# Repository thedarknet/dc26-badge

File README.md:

# dc26-badge
Darknet Industries Badge for Defcon 26

Firmware directory has STM32 and ESP32 firmware

hardware has:

* Darknet dc 26 eagle component library library
* Eagle files for board design
* docs for all components on the board plus a number of others that were considered

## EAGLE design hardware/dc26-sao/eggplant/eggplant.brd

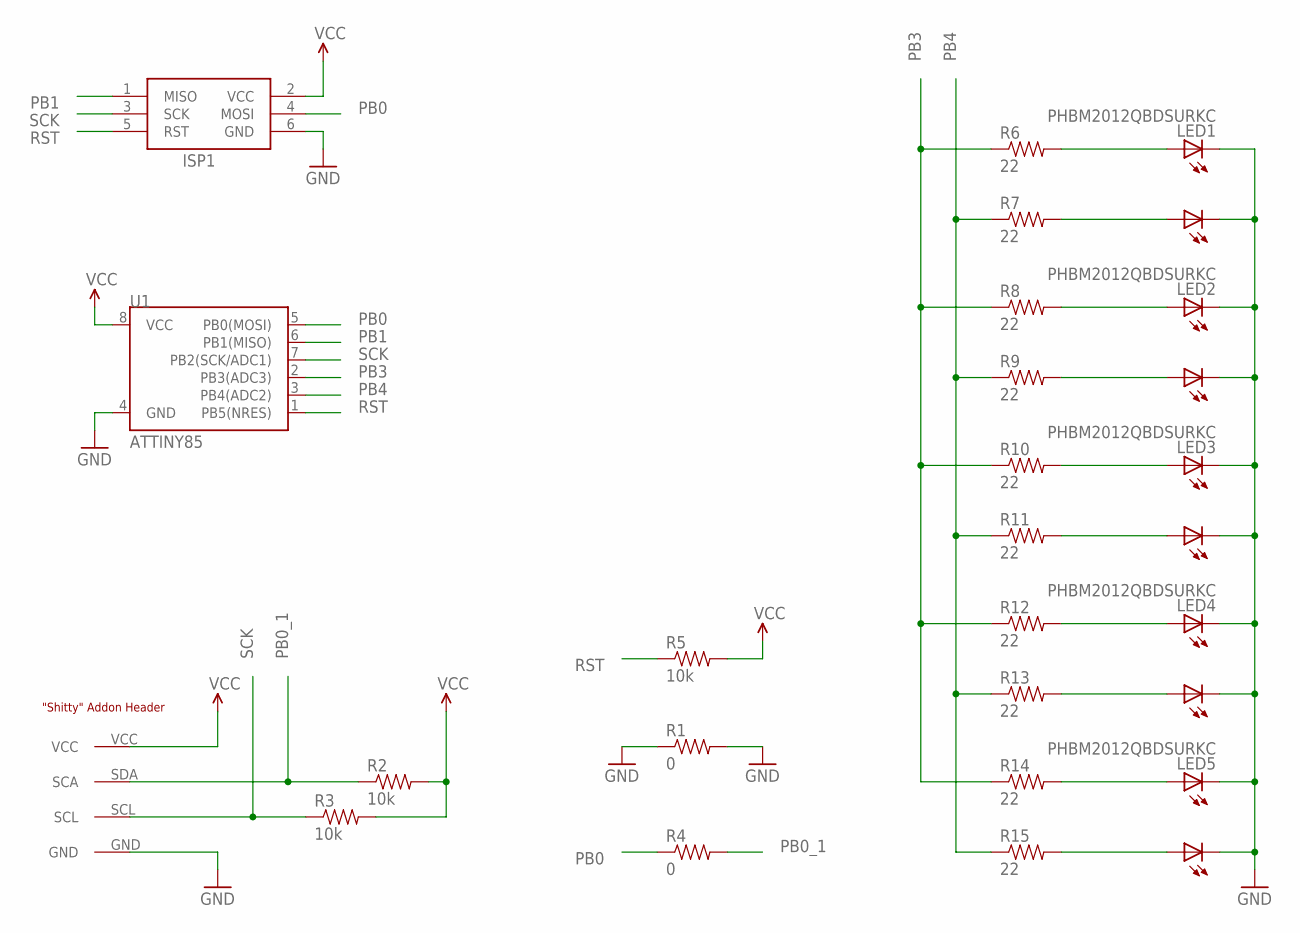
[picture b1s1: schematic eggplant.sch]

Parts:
ISP1: AVRISPPOGO; AVRISP-POGO
LED1, LED2, LED3, LED4, LED5: PHBM2012QBDSURKC; 0805-DUALLED
R1, R4: 0; 0805
R2, R3, R5: 10k; 0603-RES
R6, R7, R8, R9, R10, R11, R12, R13, R14, R15: 22; 0603-RES
U1: ATTINY85; SO08-EIAJ
U$1: ADDONSC_ADDON_SMD; SC_ADDON_SMD

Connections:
GND: ISP1.6 (GND), LED1.CB (C1), LED1.CR (C2), LED2.CB (C1), LED2.CR (C2), LED3.CB (C1), LED3.CR (C2), LED4.CB (C1), LED4.CR (C2), LED5.CB (C1), LED5.CR (C2), R1.1, R1.2, U1.4 (GND), U$1.GND
unnamed: LED1.AB (A1), R6.2
unnamed: LED1.AR (A2), R7.2
unnamed: LED2.AB (A1), R8.2
unnamed: LED2.AR (A2), R9.2
unnamed: LED3.AB (A1), R10.2
unnamed: LED3.AR (A2), R11.2
unnamed: LED4.AB (A1), R12.2
unnamed: LED4.AR (A2), R13.2
unnamed: LED5.AB (A1), R14.2
unnamed: LED5.AR (A2), R15.2
PB0: ISP1.4 (MOSI), R4.1, U1.5 (PB0(MOSI))
PB0_1: R2.1, R4.2, U$1.SDA (SCA)
PB1: ISP1.1 (MISO), U1.6 (PB1(MISO))
PB3: R6.1, R8.1, R10.1, R12.1, R14.1, U1.2 (PB3(ADC3))
PB4: R7.1, R9.1, R11.1, R13.1, R15.1, U1.3 (PB4(ADC2))
RST: ISP1.5 (RST), R5.1, U1.1 (PB5(NRES))
SCK: ISP1.3 (SCK), R3.1, U1.7 (PB2(SCK/ADC1)), U$1.SCL
VCC: ISP1.2 (VCC), R2.2, R3.2, R5.2, U1.8 (VCC), U$1.VCC

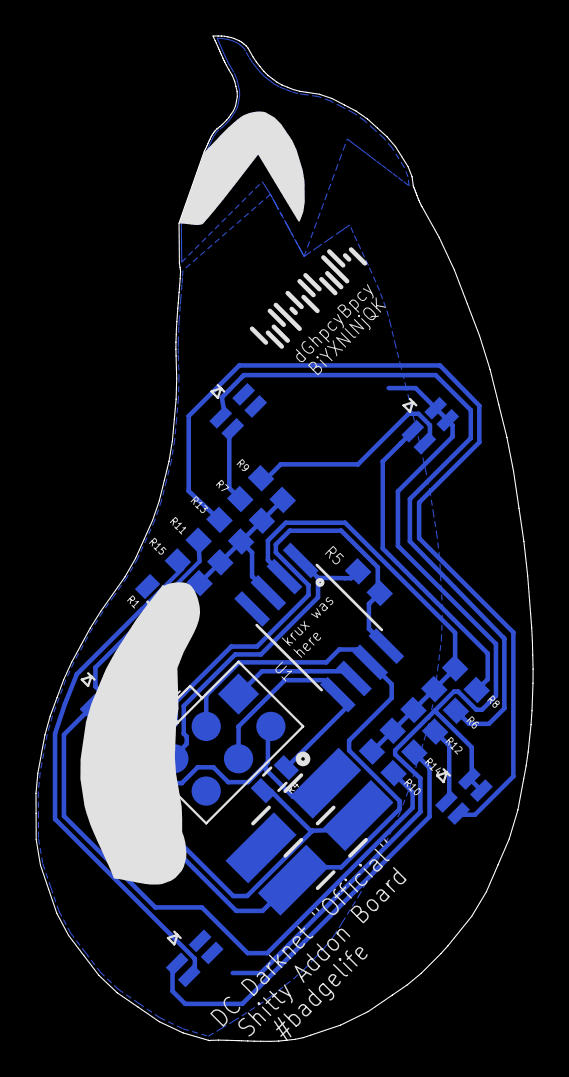
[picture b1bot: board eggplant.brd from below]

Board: 2 copper layers, 27.6 x 55.9 mm, 23 parts (22 on the bottom side), 19 nets.

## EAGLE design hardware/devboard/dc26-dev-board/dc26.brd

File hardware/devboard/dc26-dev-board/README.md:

The darknet board for 2018 (darknet-7) was dc26.brd/sch.
* Things I have not fixed yet:
 * The standard 3mm LEDs are backwards.

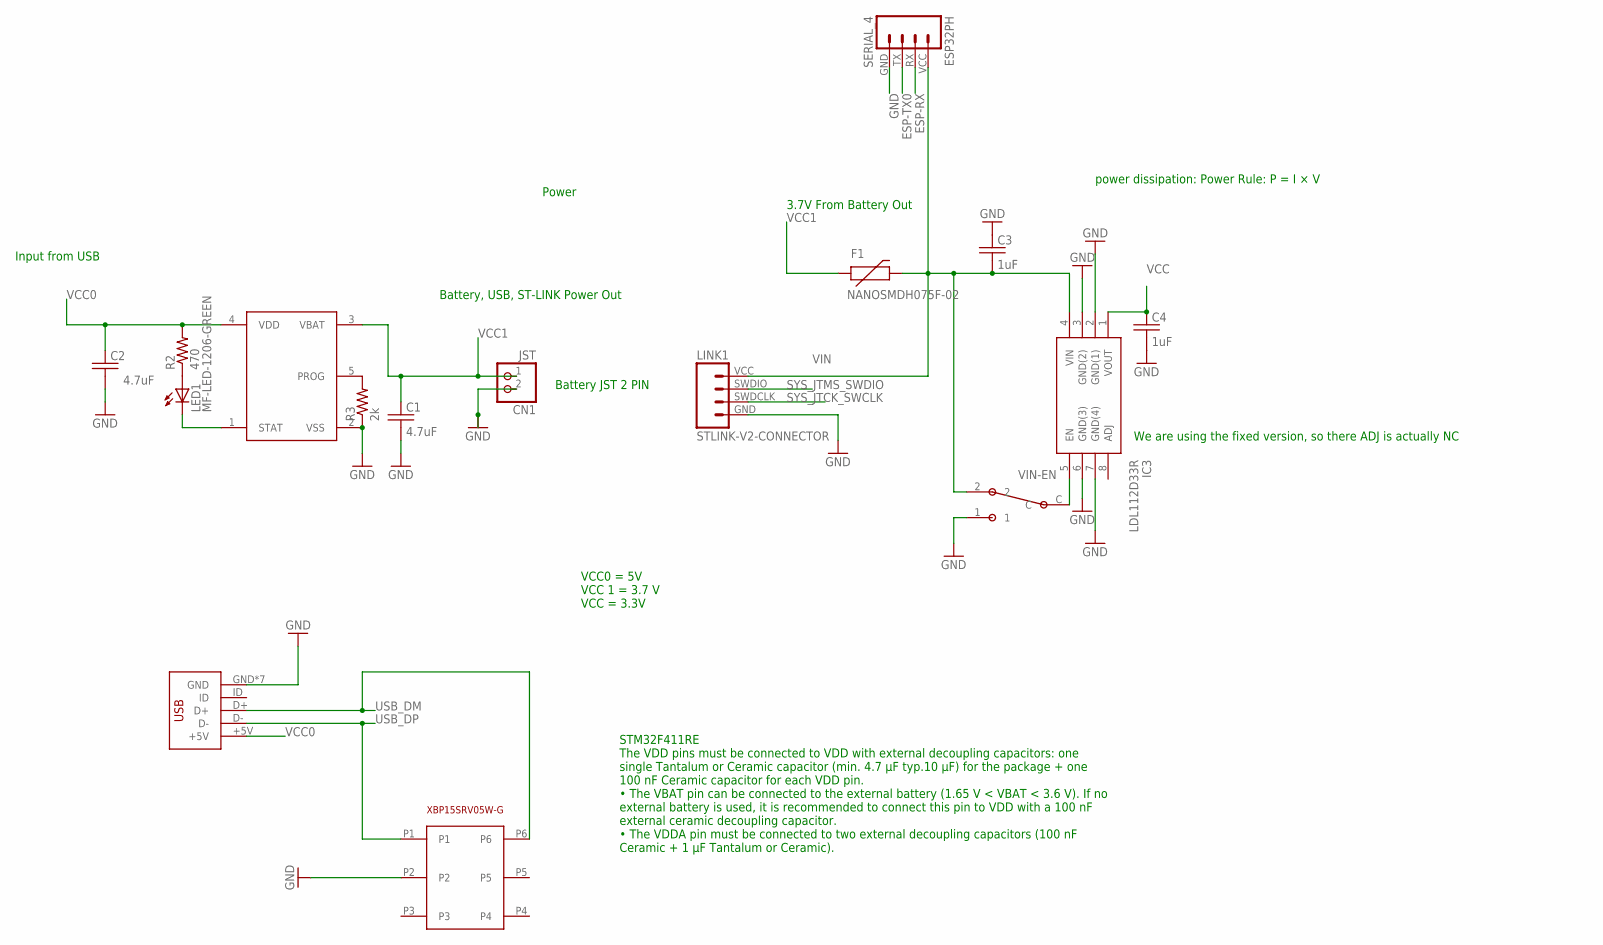
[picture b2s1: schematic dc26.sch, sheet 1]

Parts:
C1, C2: 4.7uF; C0805
C3, C4: 1uF; C0805
CHARGE: MCP73831; SOT23-5
CN1: JST; JST-PH-2-THM-RA
ESP32PH: SERIAL_4; SERIAL_HEADER_4
F1: NANOSMDH075F-02; PTC-1206
IC3: LDL112D33R; SOIC127P600X175-8N
LED1: MF-LED-1206-GREEN; LED-1206
LINK1: STLINK-V2-CONNECTOR; 1X04
P1: SPDT_SSAJ120100
R2: 470; 0805
R3: 2k; 0805
U$17: XBP15SRV05W-G; SOT-26P-XBP15SRV05W-G
USB: DX4R005JJ2DX4R005JJ2; DX4R005JJ2

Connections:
ESP-RX: ESP32PH.RX; also elsewhere on the board
ESP-TX0: ESP32PH.TX; also elsewhere on the board
GND: C1.2, C2.2, C3.1, C4.2, CHARGE.2 (VSS), CN1.2 (1), ESP32PH.GND, IC3.2 (GND(1)), IC3.3 (GND(2)), IC3.6 (GND(3)), IC3.7 (GND(4)), LINK1.GND, P1.1, R3.1, U$17.P2, USB.GND, USB.P$6 (GND), USB.P$7 (GND), USB.P$8 (GND), USB.P$9 (GND), USB.P$10 (GND), USB.P$11 (GND); also elsewhere on the board
unnamed: LED1.A, R2.1
unnamed: CHARGE.5 (PROG), R3.2
unnamed: CHARGE.1 (STAT), LED1.C
SYS_JTCK_SWCLK: LINK1.SWDCLK; also elsewhere on the board
SYS_JTMS_SWDIO: LINK1.SWDIO; also elsewhere on the board
USB_DM: U$17.P6, USB.D+; also elsewhere on the board
USB_DP: U$17.P1, USB.D-; also elsewhere on the board
VCC: C4.1, IC3.1 (VOUT); also elsewhere on the board
VCC0: C2.1, CHARGE.4 (VDD), R2.2, USB.+5V
VCC1: C1.1, CHARGE.3 (VBAT), CN1.1 (2), F1.1; also elsewhere on the board
VIN: C3.2, ESP32PH.VCC, F1.2, IC3.4 (VIN), LINK1.VCC, P1.2; also elsewhere on the board
VIN-EN: IC3.5 (EN), P1.C; also elsewhere on the board

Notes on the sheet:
Input from USB
Battery JST 2 PIN
Battery, USB, ST-LINK Power Out
power dissipation: Power Rule: P = I × V
3.7V From Battery Out
VCC0 = 5V VCC 1 = 3.7 V VCC = 3.3V
Power
STM32F411RE The VDD pins must be connected to VDD with external decoupling capacitors: one single Tantalum or Ceramic capacitor (min. 4.7 μF typ.10 μF) for the package + one 100 nF Ceramic capacitor for each VDD pin. • The VBAT pin can be connected to the external battery (1.65 V < VBAT < 3.6 V). I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
We are using the fixed version, so there ADJ is actually NC

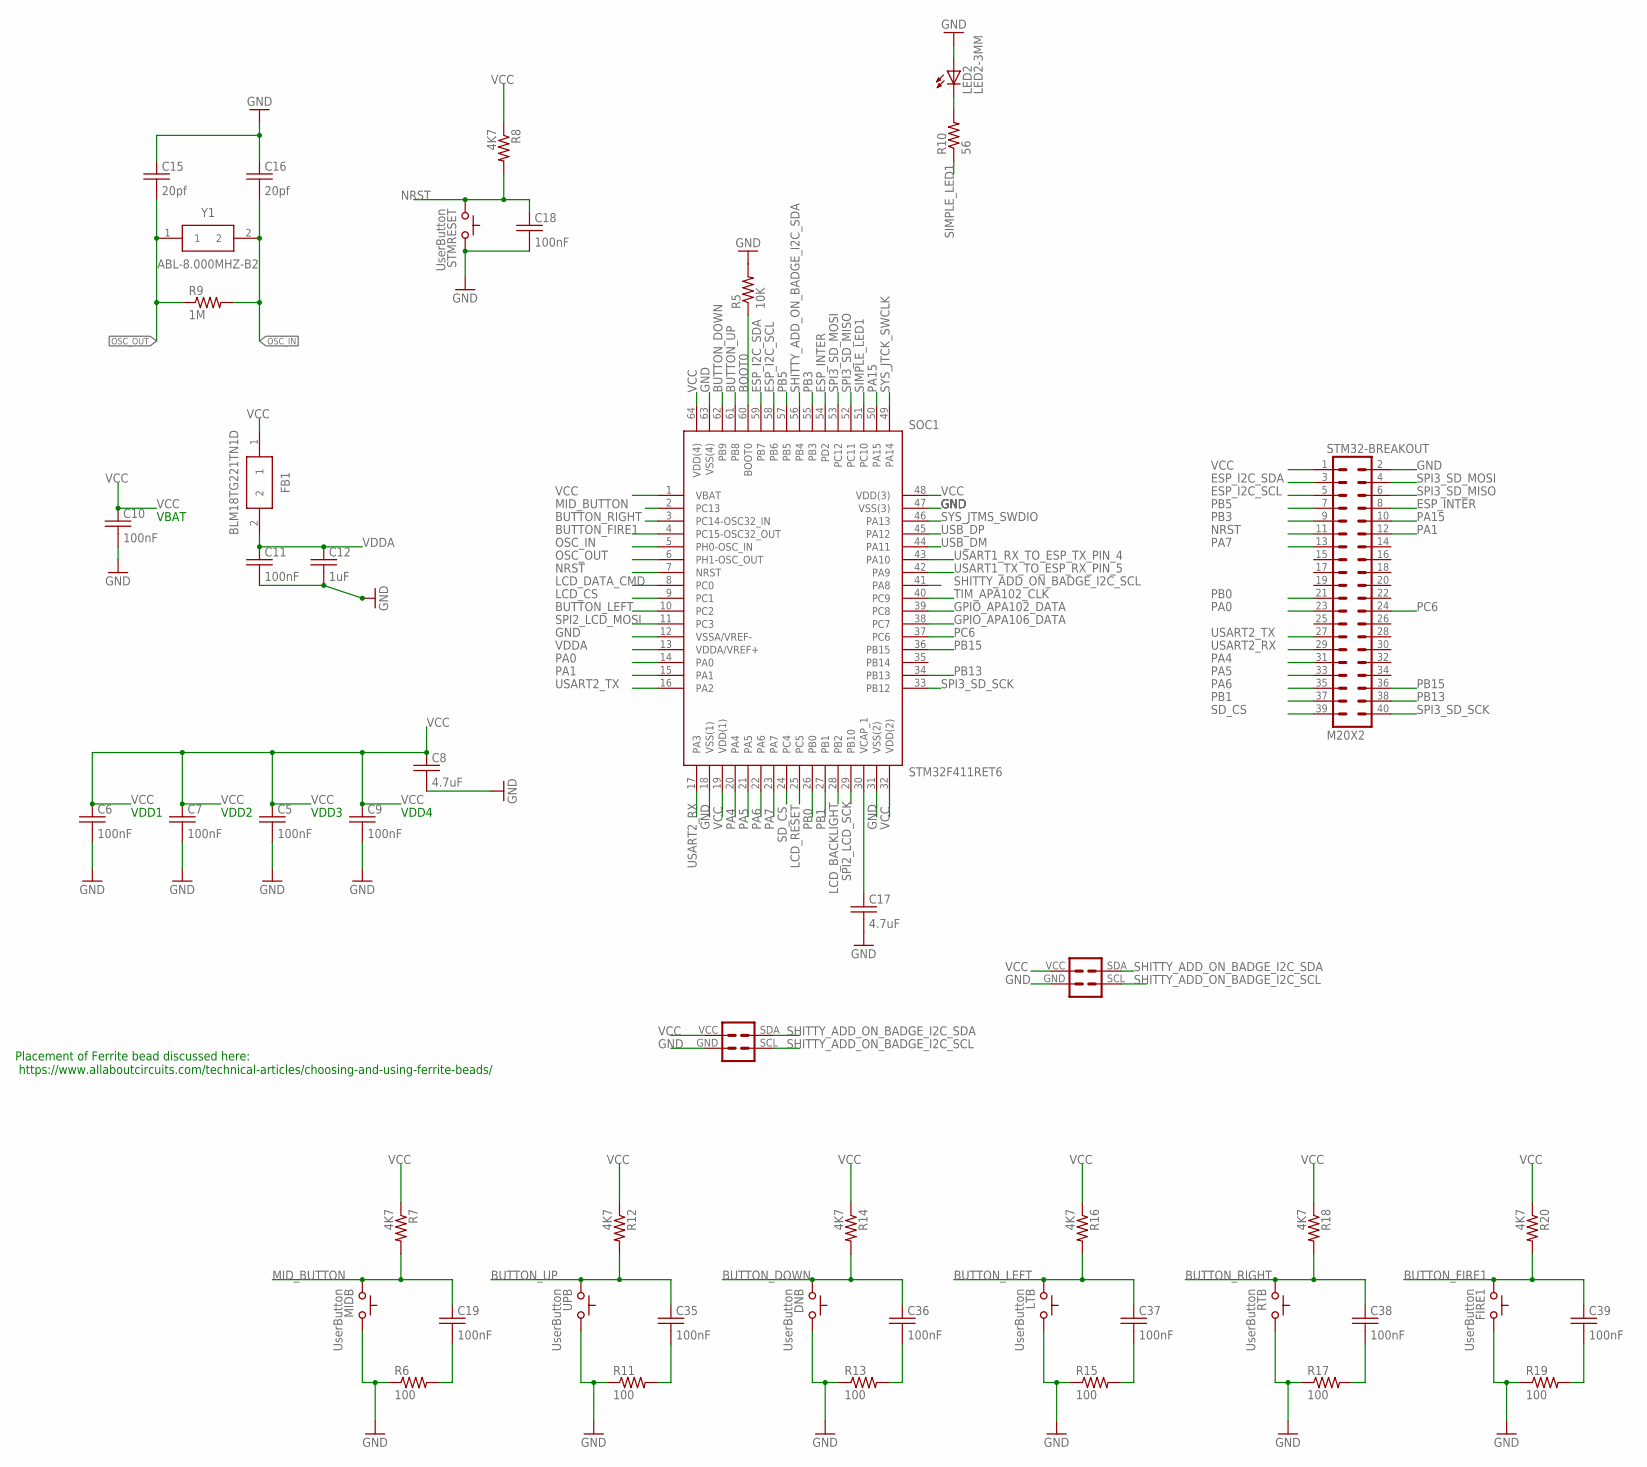
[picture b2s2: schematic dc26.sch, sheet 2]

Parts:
C5, C6, C7, C9, C10, C11, C18, C19, C35, C36, C37, C38, C39: 100nF; C0805
C8, C17: 4.7uF; C0805
C12: 1uF; C0805
C15, C16: 20pf; C0805
DNB: UserButton; TACTILE-2PIN-NARROW
FB1: BLM18TG221TN1D; BEADC1608X75N
FIRE1: UserButton; TACTILE-2PIN-NARROW
J1, J2: DC26 Shitty AddOn; DC26SHITTY_ADDON_CONNECTOR
LED2: LED2-3MM; LED3MM
LTB: UserButton; TACTILE-2PIN-NARROW
MIDB: UserButton; TACTILE-2PIN-NARROW
R5: 10K; 0805
R6, R11, R13, R15, R17, R19: 100; 0805
R7, R8, R12, R14, R16, R18, R20: 4K7; 0805
R9: 1M; 0805
R10: 56; 0805
RTB: UserButton; TACTILE-2PIN-NARROW
SOC1: STM32F411RET6; QFP50P1200X1200X160-64N
STM32-BREAKOUT: M20X2; 2X20
STMRESET: UserButton; TACTILE-2PIN-NARROW
UPB: UserButton; TACTILE-2PIN-NARROW
Y1: ABL-8.000MHZ-B2; HC/49US_(AT49)PTH

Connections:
BOOT0: R5.1, SOC1.60 (BOOT0)
BUTTON_DOWN: C36.1, DNB.P$2 (C), R14.2, SOC1.62 (PB9)
BUTTON_FIRE1: C39.1, FIRE1.P$2 (C), R20.2, SOC1.4 (PC15-OSC32_OUT)
BUTTON_LEFT: C37.1, LTB.P$2 (C), R16.2, SOC1.10 (PC2)
BUTTON_RIGHT: C38.1, R18.2, RTB.P$2 (C), SOC1.3 (PC14-OSC32_IN)
BUTTON_UP: C35.1, R12.2, SOC1.61 (PB8), UPB.P$2 (C)
ESP_I2C_SCL: SOC1.58 (PB6), STM32-BREAKOUT.5; also elsewhere on the board
ESP_I2C_SDA: SOC1.59 (PB7), STM32-BREAKOUT.3; also elsewhere on the board
ESP_INTER: SOC1.54 (PD2), STM32-BREAKOUT.8; also elsewhere on the board
GND: C5.2, C6.2, C7.2, C8.2, C9.2, C10.2, C11.2, C12.2, C15.1, C16.1, C17.2, C18.2, DNB.P$1 (A), FIRE1.P$1 (A), J1.GND, J2.GND, LED2.A, LTB.P$1 (A), MIDB.P$1 (A), R5.2, R6.1, R11.1, R13.1, R15.1, R17.1, R19.1, RTB.P$1 (A), SOC1.12 (VSSA/VREF-), SOC1.18 (VSS(1)), SOC1.31 (VSS(2)), SOC1.47 (VSS(3)), SOC1.63 (VSS(4)), STM32-BREAKOUT.2, STMRESET.P$1 (A), UPB.P$1 (A); also elsewhere on the board
GPIO_APA102_DATA: SOC1.39 (PC8); also elsewhere on the board
GPIO_APA106_DATA: SOC1.38 (PC7); also elsewhere on the board
LCD_BACKLIGHT: SOC1.28 (PB2); also elsewhere on the board
LCD_CS: SOC1.9 (PC1); also elsewhere on the board
LCD_DATA_CMD: SOC1.8 (PC0); also elsewhere on the board
LCD_RESET: SOC1.25 (PC5); also elsewhere on the board
MID_BUTTON: C19.1, MIDB.P$2 (C), R7.2, SOC1.2 (PC13)
unnamed: C19.2, R6.2
unnamed: C17.1, SOC1.30 (VCAP_1)
unnamed: LED2.K (C), R10.2
unnamed: C35.2, R11.2
unnamed: C36.2, R13.2
unnamed: C37.2, R15.2
unnamed: C38.2, R17.2
unnamed: C39.2, R19.2
NRST: C18.1, R8.2, SOC1.7 (NRST), STM32-BREAKOUT.11, STMRESET.P$2 (C)
OSC_IN: C16.2, R9.2, SOC1.5 (PH0-OSC_IN), Y1.2
OSC_OUT: C15.2, R9.1, SOC1.6 (PH1-OSC_OUT), Y1.1
PA0: SOC1.14 (PA0), STM32-BREAKOUT.23
PA1: SOC1.15 (PA1), STM32-BREAKOUT.12
PA4: SOC1.20 (PA4), STM32-BREAKOUT.31
PA5: SOC1.21 (PA5), STM32-BREAKOUT.33
PA6: SOC1.22 (PA6), STM32-BREAKOUT.35
PA7: SOC1.23 (PA7), STM32-BREAKOUT.13
PA15: SOC1.50 (PA15), STM32-BREAKOUT.10
PB0: SOC1.26 (PB0), STM32-BREAKOUT.21
PB1: SOC1.27 (PB1), STM32-BREAKOUT.37
PB3: SOC1.55 (PB3), STM32-BREAKOUT.9
PB5: SOC1.57 (PB5), STM32-BREAKOUT.7
PB13: SOC1.34 (PB13), STM32-BREAKOUT.38
PB15: SOC1.36 (PB15), STM32-BREAKOUT.36
PC6: SOC1.37 (PC6), STM32-BREAKOUT.24
SD_CS: SOC1.24 (PC4), STM32-BREAKOUT.39; also elsewhere on the board
SHITTY_ADD_ON_BADGE_I2C_SCL: J1.SCL, J2.SCL, SOC1.41 (PA8)
SHITTY_ADD_ON_BADGE_I2C_SDA: J1.SDA, J2.SDA, SOC1.56 (PB4)
SIMPLE_LED1: R10.1, SOC1.51 (PC10)
SPI2_LCD_MOSI: SOC1.11 (PC3); also elsewhere on the board
SPI2_LCD_SCK: SOC1.29 (PB10); also elsewhere on the board
SPI3_SD_MISO: SOC1.52 (PC11), STM32-BREAKOUT.6; also elsewhere on the board
SPI3_SD_MOSI: SOC1.53 (PC12), STM32-BREAKOUT.4; also elsewhere on the board
SPI3_SD_SCK: SOC1.33 (PB12), STM32-BREAKOUT.40; also elsewhere on the board
SYS_JTCK_SWCLK: SOC1.49 (PA14); also elsewhere on the board
SYS_JTMS_SWDIO: SOC1.46 (PA13); also elsewhere on the board
TIM_APA102_CLK: SOC1.40 (PC9); also elsewhere on the board
USART1_RX_TO_ESP_TX_PIN_4: SOC1.43 (PA10); also elsewhere on the board
USART1_TX_TO_ESP_RX_PIN_5: SOC1.42 (PA9); also elsewhere on the board
USART2_RX: SOC1.17 (PA3), STM32-BREAKOUT.29
USART2_TX: SOC1.16 (PA2), STM32-BREAKOUT.27
USB_DM: SOC1.44 (PA11); also elsewhere on the board
USB_DP: SOC1.45 (PA12); also elsewhere on the board
VCC: C5.1, C6.1, C7.1, C8.1, C9.1, C10.1, FB1.1, J1.VCC, J2.VCC, R7.1, R8.1, R12.1, R14.1, R16.1, R18.1, R20.1, SOC1.1 (VBAT), SOC1.19 (VDD(1)), SOC1.32 (VDD(2)), SOC1.48 (VDD(3)), SOC1.64 (VDD(4)), STM32-BREAKOUT.1; also elsewhere on the board
VDDA: C11.1, C12.1, FB1.2, SOC1.13 (VDDA/VREF+)

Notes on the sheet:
Placement of Ferrite bead discussed here: https://www.allaboutcircuits.com/technical-articles/choosing-and-using-ferrite-beads/
VBAT
VDD1
VDD2
VDD3
VDD4

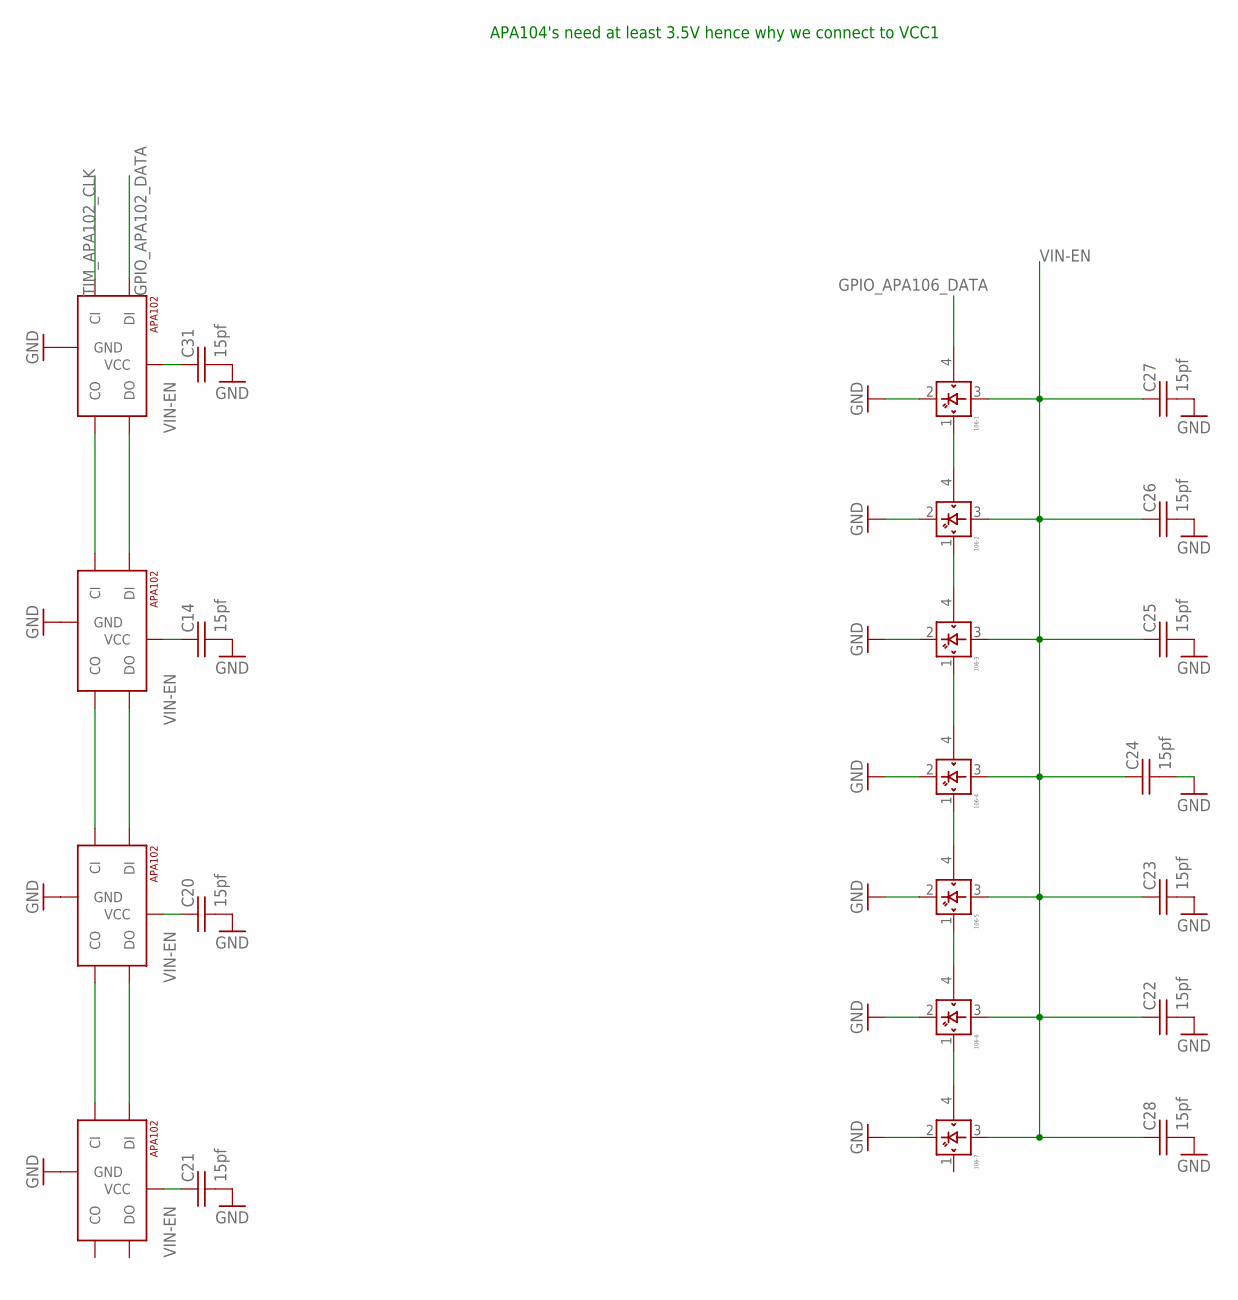
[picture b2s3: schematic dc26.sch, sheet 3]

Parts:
102-1, 102-2, 102-3, 102-4: APA1025050; APA102_5050
106-1, 106-2, 106-3, 106-4, 106-5, 106-6, 106-7: APA-106; WS2812F5_STRAIGHT
C14, C20, C21, C22, C23, C24, C25, C26, C27, C28, C31: 15pf; C0805

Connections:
GND: 102-1.6 (GND), 102-2.6 (GND), 102-3.6 (GND), 102-4.6 (GND), 106-1.2 (GND), 106-2.2 (GND), 106-3.2 (GND), 106-4.2 (GND), 106-5.2 (GND), 106-6.2 (GND), 106-7.2 (GND), C14.2, C20.2, C21.2, C22.2, C23.2, C24.2, C25.2, C26.2, C27.2, C28.2, C31.2; also elsewhere on the board
GPIO_APA102_DATA: 102-1.4 (DI); also elsewhere on the board
GPIO_APA106_DATA: 106-1.4 (DIN); also elsewhere on the board
unnamed: 102-1.2 (CO), 102-2.5 (CI)
unnamed: 102-2.2 (CO), 102-3.5 (CI)
unnamed: 102-3.2 (CO), 102-4.5 (CI)
unnamed: 102-3.3 (DO), 102-4.4 (DI)
unnamed: 102-2.3 (DO), 102-3.4 (DI)
unnamed: 102-1.3 (DO), 102-2.4 (DI)
unnamed: 106-1.1 (DOUT), 106-2.4 (DIN)
unnamed: 106-2.1 (DOUT), 106-3.4 (DIN)
unnamed: 106-3.1 (DOUT), 106-4.4 (DIN)
unnamed: 106-4.1 (DOUT), 106-5.4 (DIN)
unnamed: 106-5.1 (DOUT), 106-6.4 (DIN)
unnamed: 106-6.1 (DOUT), 106-7.4 (DIN)
TIM_APA102_CLK: 102-1.5 (CI); also elsewhere on the board
VIN-EN: 102-1.1 (VCC), 102-2.1 (VCC), 102-3.1 (VCC), 102-4.1 (VCC), 106-1.3 (VDD), 106-2.3 (VDD), 106-3.3 (VDD), 106-4.3 (VDD), 106-5.3 (VDD), 106-6.3 (VDD), 106-7.3 (VDD), C14.1, C20.1, C21.1, C22.1, C23.1, C24.1, C25.1, C26.1, C27.1, C28.1, C31.1; also elsewhere on the board

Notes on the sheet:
APA104's need at least 3.5V hence why we connect to VCC1

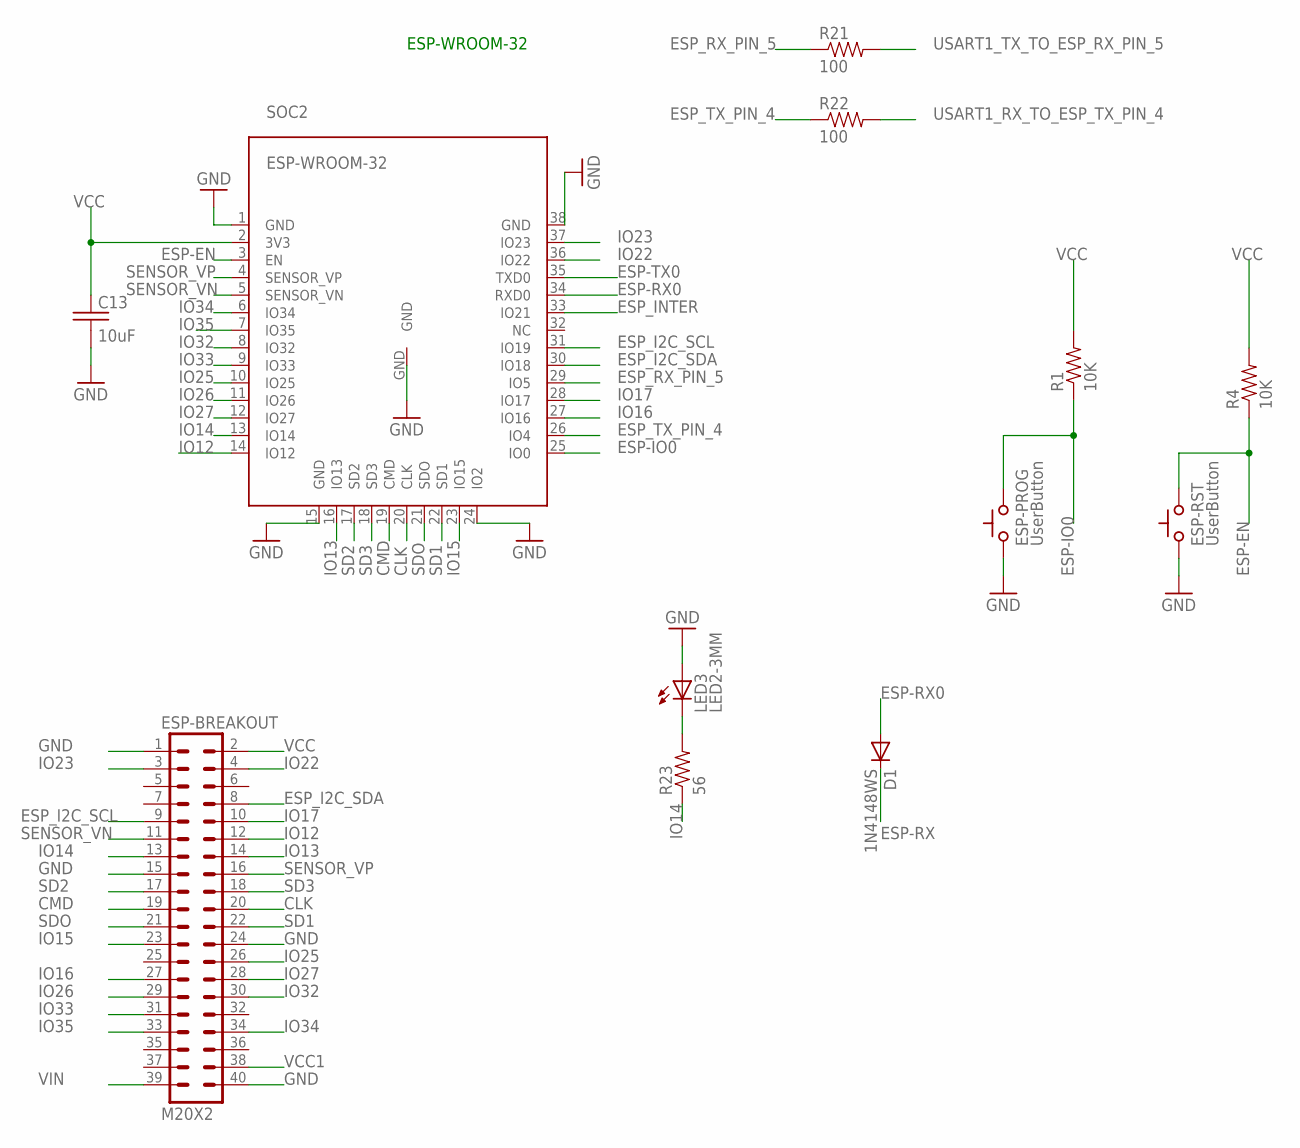
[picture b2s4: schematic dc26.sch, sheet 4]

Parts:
C13: 10uF; C0805
D1: 1N4148WS; SOD-323
ESP-BREAKOUT: M20X2; 2X20
ESP-PROG: UserButton; TACTILE-2PIN-NARROW
ESP-RST: UserButton; TACTILE-2PIN-NARROW
LED3: LED2-3MM; LED3MM
R1, R4: 10K; 0805
R21, R22: 100; 0805
R23: 56; 0805
SOC2: ESP-WROOM-32

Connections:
CLK: ESP-BREAKOUT.20, SOC2.20 (CLK)
CMD: ESP-BREAKOUT.19, SOC2.19 (CMD)
ESP-EN: ESP-RST.P$1 (A), R4.1, SOC2.3 (EN)
ESP-IO0: ESP-PROG.P$1 (A), R1.1, SOC2.25 (IO0)
ESP-RX: D1.1 (C); also elsewhere on the board
ESP-RX0: D1.2 (A), SOC2.34 (RXD0)
ESP-TX0: SOC2.35 (TXD0); also elsewhere on the board
ESP_I2C_SCL: ESP-BREAKOUT.9, SOC2.31 (IO19); also elsewhere on the board
ESP_I2C_SDA: ESP-BREAKOUT.8, SOC2.30 (IO18); also elsewhere on the board
ESP_INTER: SOC2.33 (IO21); also elsewhere on the board
ESP_RX_PIN_5: R21.1, SOC2.29 (IO5)
ESP_TX_PIN_4: R22.1, SOC2.26 (IO4)
GND: C13.2, ESP-BREAKOUT.1, ESP-BREAKOUT.15, ESP-BREAKOUT.24, ESP-BREAKOUT.40, ESP-PROG.P$2 (C), ESP-RST.P$2 (C), LED3.A, SOC2.1 (GND), SOC2.15 (GND), SOC2.24 (IO2), SOC2.38 (GND), SOC2.GND; also elsewhere on the board
IO12: ESP-BREAKOUT.12, SOC2.14 (IO12)
IO13: ESP-BREAKOUT.14, SOC2.16 (IO13)
IO14: ESP-BREAKOUT.13, R23.1, SOC2.13 (IO14)
IO15: ESP-BREAKOUT.23, SOC2.23 (IO15)
IO16: ESP-BREAKOUT.27, SOC2.27 (IO16)
IO17: ESP-BREAKOUT.10, SOC2.28 (IO17)
IO22: ESP-BREAKOUT.4, SOC2.36 (IO22)
IO23: ESP-BREAKOUT.3, SOC2.37 (IO23)
IO25: ESP-BREAKOUT.26, SOC2.10 (IO25)
IO26: ESP-BREAKOUT.29, SOC2.11 (IO26)
IO27: ESP-BREAKOUT.28, SOC2.12 (IO27)
IO32: ESP-BREAKOUT.30, SOC2.8 (IO32)
IO33: ESP-BREAKOUT.31, SOC2.9 (IO33)
IO34: ESP-BREAKOUT.34, SOC2.6 (IO34)
IO35: ESP-BREAKOUT.33, SOC2.7 (IO35)
unnamed: LED3.K (C), R23.2
SD1: ESP-BREAKOUT.22, SOC2.22 (SD1)
SD2: ESP-BREAKOUT.17, SOC2.17 (SD2)
SD3: ESP-BREAKOUT.18, SOC2.18 (SD3)
SDO: ESP-BREAKOUT.21, SOC2.21 (SDO)
SENSOR_VN: ESP-BREAKOUT.11, SOC2.5 (SENSOR_VN)
SENSOR_VP: ESP-BREAKOUT.16, SOC2.4 (SENSOR_VP)
USART1_RX_TO_ESP_TX_PIN_4: R22.2; also elsewhere on the board
USART1_TX_TO_ESP_RX_PIN_5: R21.2; also elsewhere on the board
VCC: C13.1, ESP-BREAKOUT.2, R1.2, R4.2, SOC2.2 (3V3); also elsewhere on the board
VCC1: ESP-BREAKOUT.38; also elsewhere on the board
VIN: ESP-BREAKOUT.39; also elsewhere on the board

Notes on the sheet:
ESP-WROOM-32

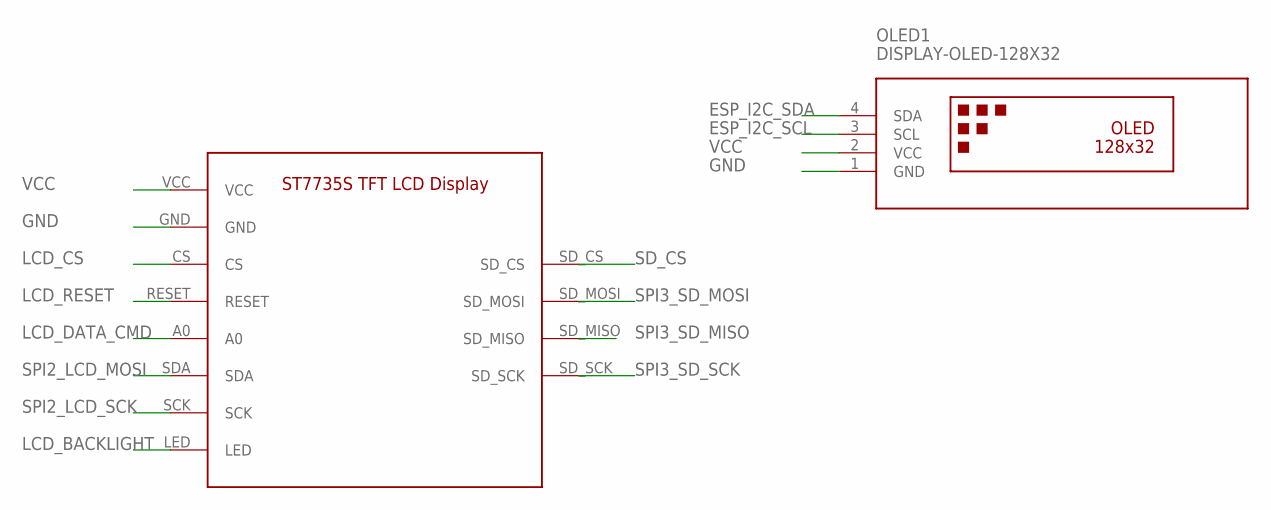
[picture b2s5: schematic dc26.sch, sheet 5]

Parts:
LCD1: ST7735S_LCD_MODULE; ST7735S_LCD_DISPLAY
OLED1: DISPLAY-OLED-128X32

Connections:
ESP_I2C_SCL: OLED1.3 (SCL); also elsewhere on the board
ESP_I2C_SDA: OLED1.4 (SDA); also elsewhere on the board
GND: LCD1.GND, OLED1.1 (GND); also elsewhere on the board
LCD_BACKLIGHT: LCD1.LED; also elsewhere on the board
LCD_CS: LCD1.CS; also elsewhere on the board
LCD_DATA_CMD: LCD1.A0; also elsewhere on the board
LCD_RESET: LCD1.RESET; also elsewhere on the board
SD_CS: LCD1.SD_CS; also elsewhere on the board
SPI2_LCD_MOSI: LCD1.SDA; also elsewhere on the board
SPI2_LCD_SCK: LCD1.SCK; also elsewhere on the board
SPI3_SD_MISO: LCD1.SD_MISO; also elsewhere on the board
SPI3_SD_MOSI: LCD1.SD_MOSI; also elsewhere on the board
SPI3_SD_SCK: LCD1.SD_SCK; also elsewhere on the board
VCC: LCD1.VCC, OLED1.2 (VCC); also elsewhere on the board

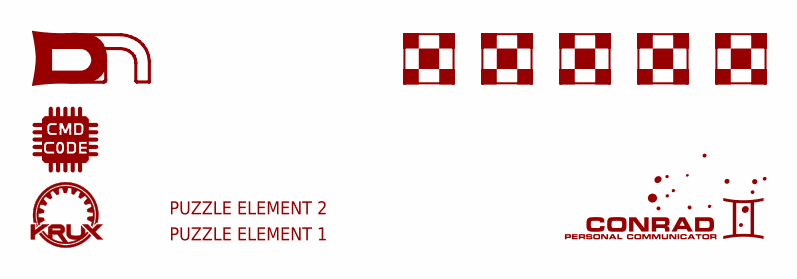
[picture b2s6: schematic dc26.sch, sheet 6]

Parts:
U$1: KRUX_LOGO
U$2: CMD_C0DE_LOGO
U$3: DC26_KRUX_PUZZLE_1; DN26_KRUX_PUZZLE_1
U$4: DC26_KRUX_PUZZLE_2; DN26_KRUX_PUZZLE_2
U$5: CONRAD_LOGO
U$6: DN_LOGODC26; DN_LOGO_DC26
U$7, U$8: FIDUCIAL_DNBOX; FIDUCIAL_BOX
U$9, U$10, U$11: FIDUCIAL_DNCORNER; FIDUCIAL_CORNER

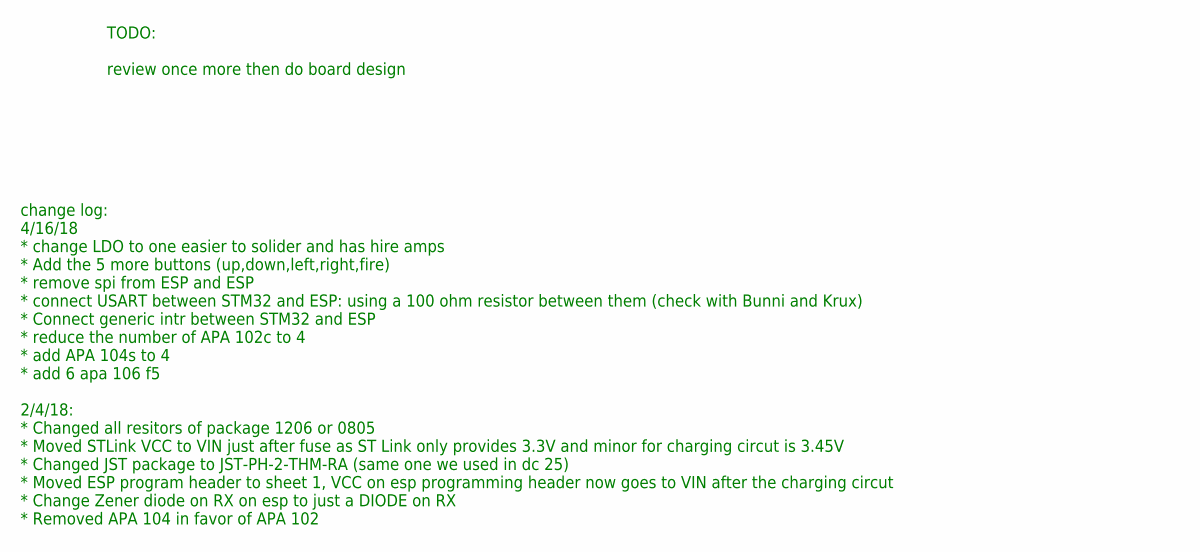
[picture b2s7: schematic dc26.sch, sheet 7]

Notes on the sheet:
change log: 4/16/18 * change LDO to one easier to solider and has hire amps * Add the 5 more buttons (up,down,left,right,fire) * remove spi from ESP and ESP * connect USART between STM32 and ESP: using a 100 ohm resistor between them (check with Bunni and Krux) * Connect generic intr between STM32 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
TODO: review once more then do board design

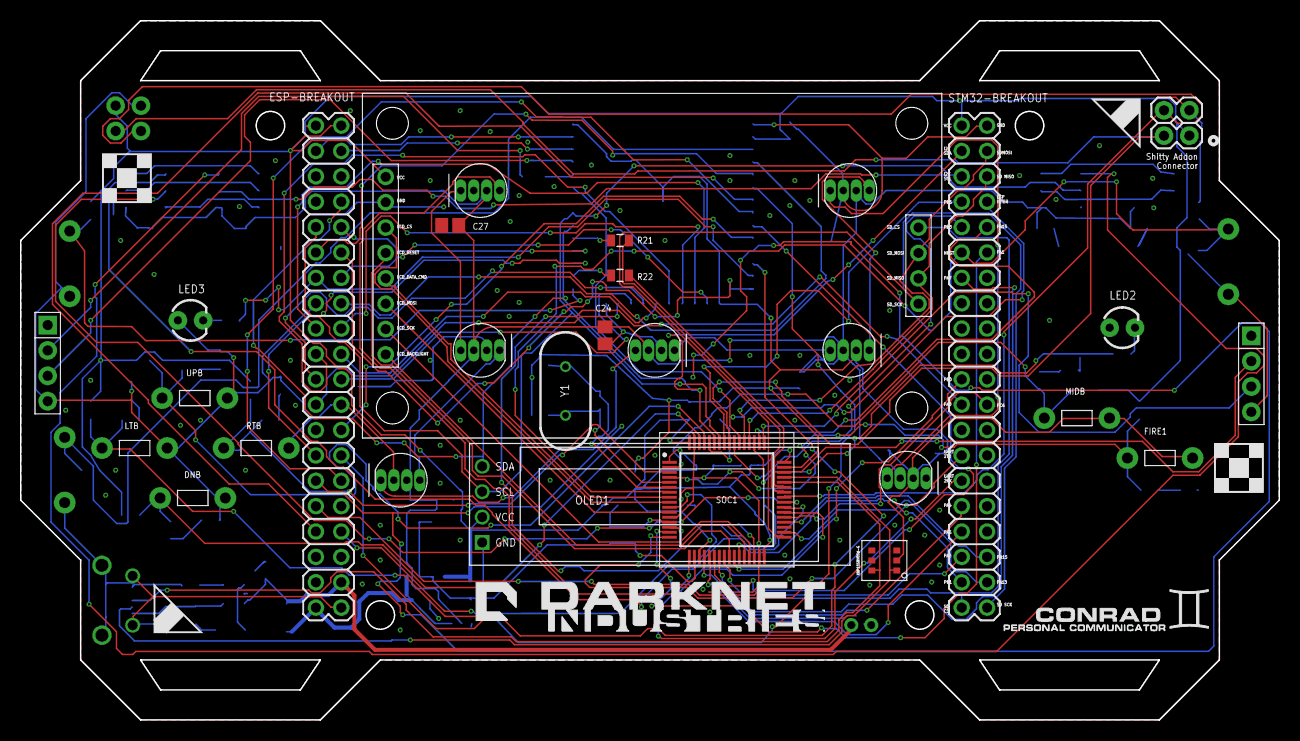
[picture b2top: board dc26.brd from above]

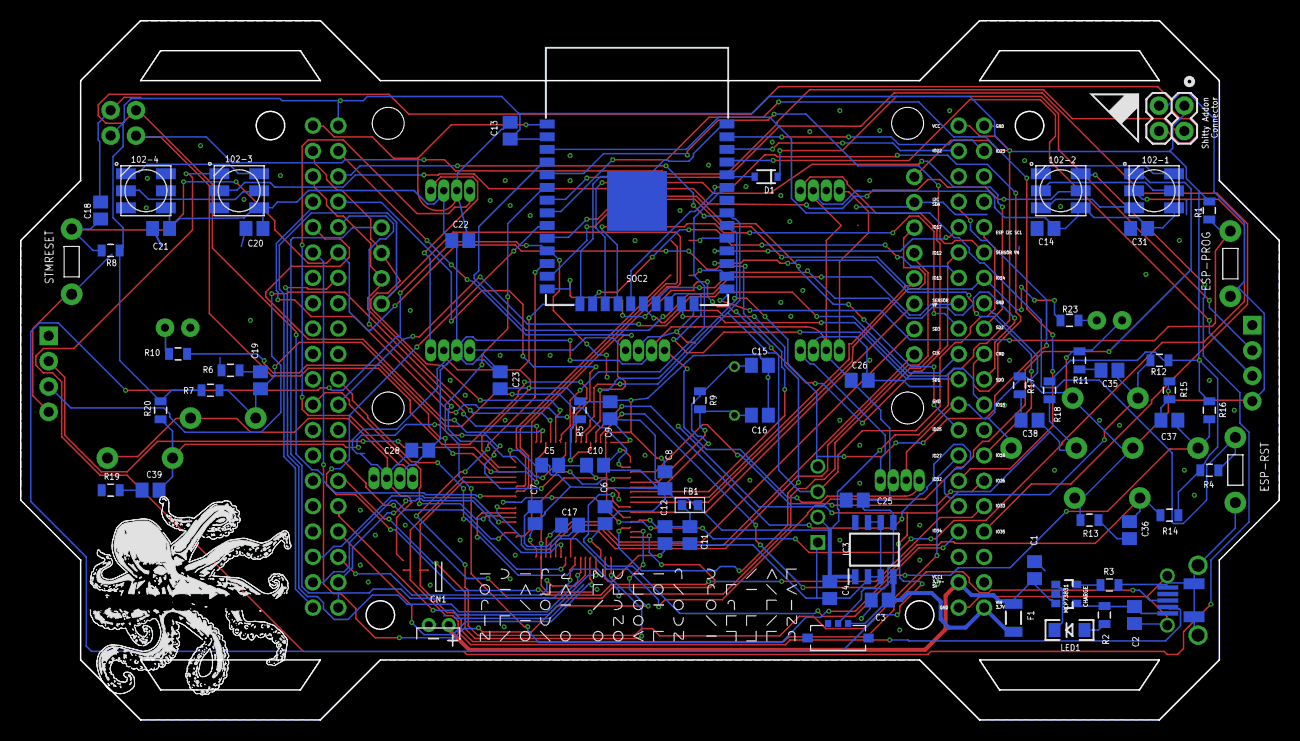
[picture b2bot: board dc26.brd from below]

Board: 2 copper layers, 126.0 x 70.0 mm, 111 parts (76 on the bottom side), 112 nets.

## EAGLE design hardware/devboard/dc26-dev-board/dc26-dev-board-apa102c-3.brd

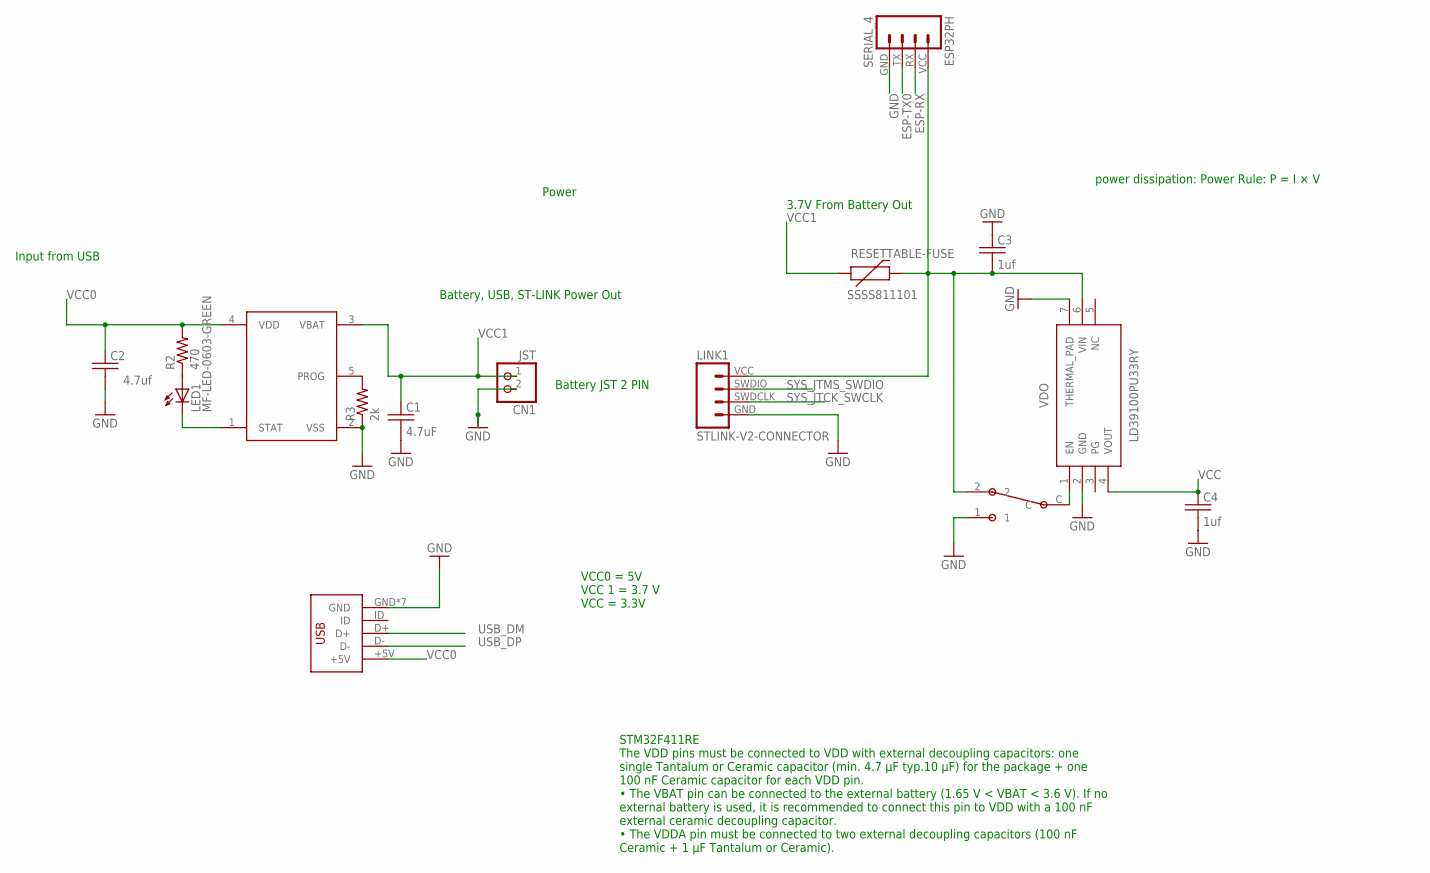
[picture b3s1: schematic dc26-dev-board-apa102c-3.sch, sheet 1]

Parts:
C1: 4.7uF; C0805
C2: 4.7uf; C0805
C3, C4: 1uf; C0805
CHARGING_CIRCUT: MCP73831; SOT23-5
CN1: JST; JST-PH-2-THM-RA
ESP32PH: SERIAL_4; SERIAL_HEADER_4
LED1: MF-LED-0603-GREEN; LED-1206
LINK1: STLINK-V2-CONNECTOR; 1X04
P1: SSSS811101; SPDT_SSAJ120100
R2: 470; 0805
R3: 2k; 0805
RESETTABLE-FUSE: SSSS811101; PTC-1206
USB: DX4R005JJ2DX4R005JJ2; DX4R005JJ2
VDO: LD39100PU33RY; SON95P300X300X90-7N

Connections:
ESP-RX: ESP32PH.RX; also elsewhere on the board
ESP-TX0: ESP32PH.TX; also elsewhere on the board
GND: C1.2, C2.2, C3.1, C4.2, CHARGING_CIRCUT.2 (VSS), CN1.2 (1), ESP32PH.GND, LINK1.GND, P1.1, R3.1, USB.GND, USB.P$6 (GND), USB.P$7 (GND), USB.P$8 (GND), USB.P$9 (GND), USB.P$10 (GND), USB.P$11 (GND), VDO.2 (GND), VDO.7 (THERMAL_PAD); also elsewhere on the board
unnamed: LED1.A, R2.1
unnamed: CHARGING_CIRCUT.5 (PROG), R3.2
unnamed: CHARGING_CIRCUT.1 (STAT), LED1.C
SYS_JTCK_SWCLK: LINK1.SWDCLK; also elsewhere on the board
SYS_JTMS_SWDIO: LINK1.SWDIO; also elsewhere on the board
USB_DM: USB.D+; also elsewhere on the board
USB_DP: USB.D-; also elsewhere on the board
VCC: C4.1, VDO.4 (VOUT); also elsewhere on the board
VCC0: C2.1, CHARGING_CIRCUT.4 (VDD), R2.2, USB.+5V
VCC1: C1.1, CHARGING_CIRCUT.3 (VBAT), CN1.1 (2), RESETTABLE-FUSE.1
VIN: C3.2, ESP32PH.VCC, LINK1.VCC, P1.2, RESETTABLE-FUSE.2, VDO.6 (VIN); also elsewhere on the board
VIN-EN: P1.C, VDO.1 (EN)

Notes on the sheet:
Input from USB
Battery JST 2 PIN
Battery, USB, ST-LINK Power Out
power dissipation: Power Rule: P = I × V
3.7V From Battery Out
VCC0 = 5V VCC 1 = 3.7 V VCC = 3.3V
Power
STM32F411RE The VDD pins must be connected to VDD with external decoupling capacitors: one single Tantalum or Ceramic capacitor (min. 4.7 μF typ.10 μF) for the package + one 100 nF Ceramic capacitor for each VDD pin. • The VBAT pin can be connected to the external battery (1.65 V < VBAT < 3.6 V). I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

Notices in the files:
parts and their libraries:
SparkFun: Licensing: CC v3.0 Share-Alike You are welcome to use this library for commercial purposes.
